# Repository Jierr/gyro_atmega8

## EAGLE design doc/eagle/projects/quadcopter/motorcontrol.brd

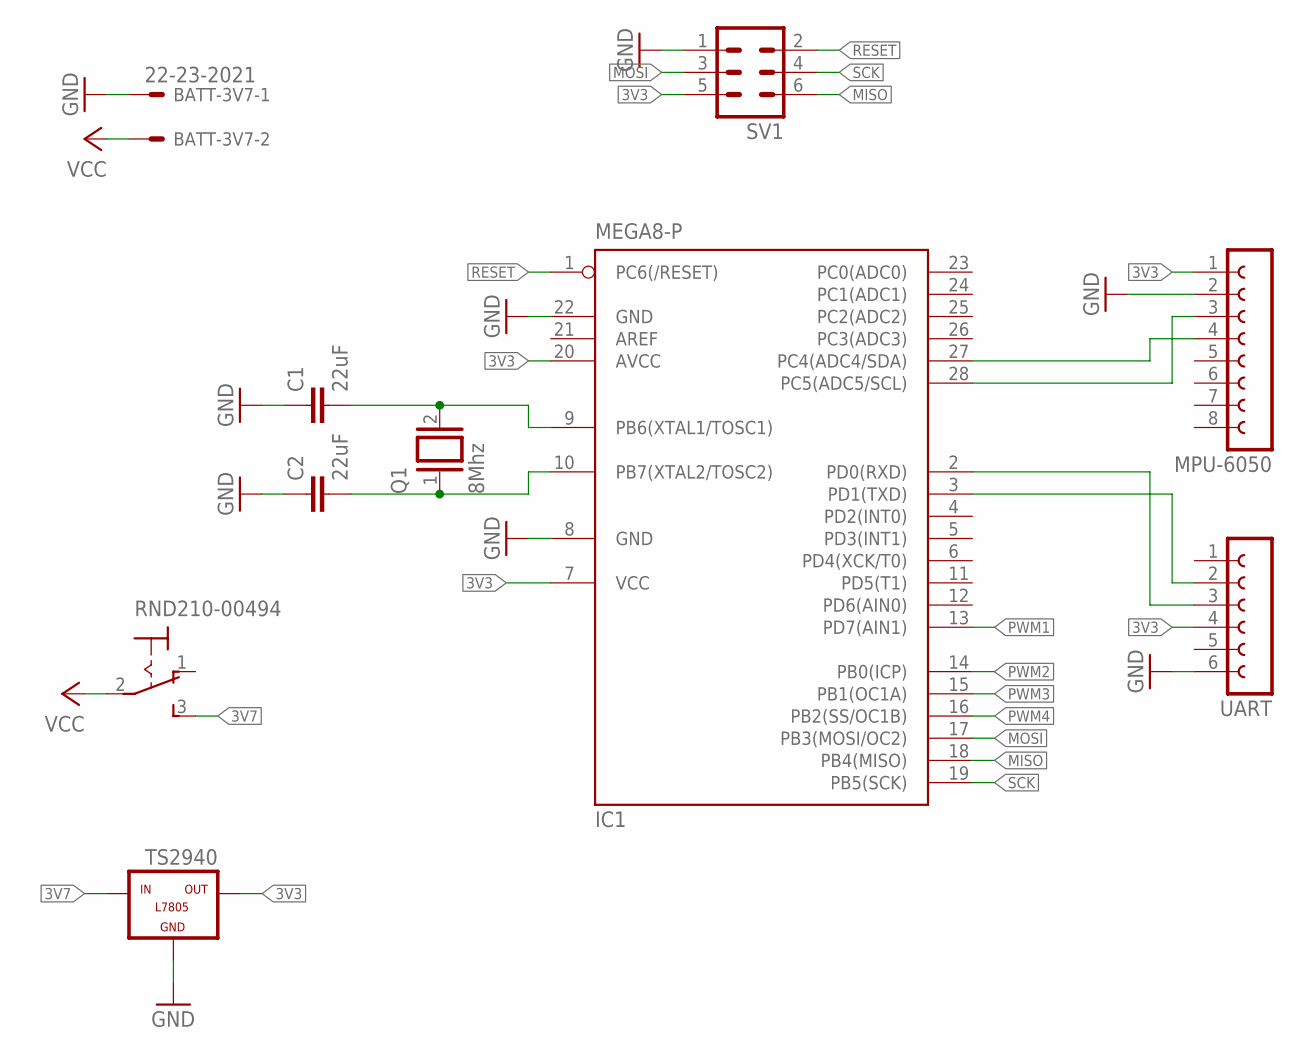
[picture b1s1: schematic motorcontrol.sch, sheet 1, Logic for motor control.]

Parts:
BATT-3V7: 22-23-2021
C1, C2: 22uF; C025-025X050
IC1: MEGA8-P; DIL28-3
MPU-6050: FE08-1; FE08
Q1: 8Mhz; QS
RND210-00494: 320-916
SV1: MA03-2
TS2940: TS2940; TO220
UART: FE06-1; FE06

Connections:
3V3: IC1.7 (VCC), IC1.20 (AVCC), MPU-6050.1, SV1.5, TS2940.3 (OUT), UART.4
3V7: RND210-00494.3 (S), TS2940.1 (IN); also elsewhere on the board
GND: BATT-3V7.1, C1.1, C2.1, IC1.8 (GND), IC1.22 (GND), MPU-6050.2, SV1.1, TS2940.2 (GND), UART.6; also elsewhere on the board
MISO: IC1.18 (PB4(MISO)), SV1.6
MOSI: IC1.17 (PB3(MOSI/OC2)), SV1.3
unnamed: C2.2, IC1.10 (PB7(XTAL2/TOSC2)), Q1.1
unnamed: C1.2, IC1.9 (PB6(XTAL1/TOSC1)), Q1.2
unnamed: IC1.28 (PC5(ADC5/SCL)), MPU-6050.3
unnamed: IC1.27 (PC4(ADC4/SDA)), MPU-6050.4
unnamed: IC1.3 (PD1(TXD)), UART.2
unnamed: IC1.2 (PD0(RXD)), UART.3
PWM1: IC1.13 (PD7(AIN1)); also elsewhere on the board
PWM2: IC1.14 (PB0(ICP)); also elsewhere on the board
PWM3: IC1.15 (PB1(OC1A)); also elsewhere on the board
PWM4: IC1.16 (PB2(SS/OC1B)); also elsewhere on the board
RESET: IC1.1 (PC6(/RESET)), SV1.2
SCK: IC1.19 (PB5(SCK)), SV1.4
VCC: BATT-3V7.2, RND210-00494.2

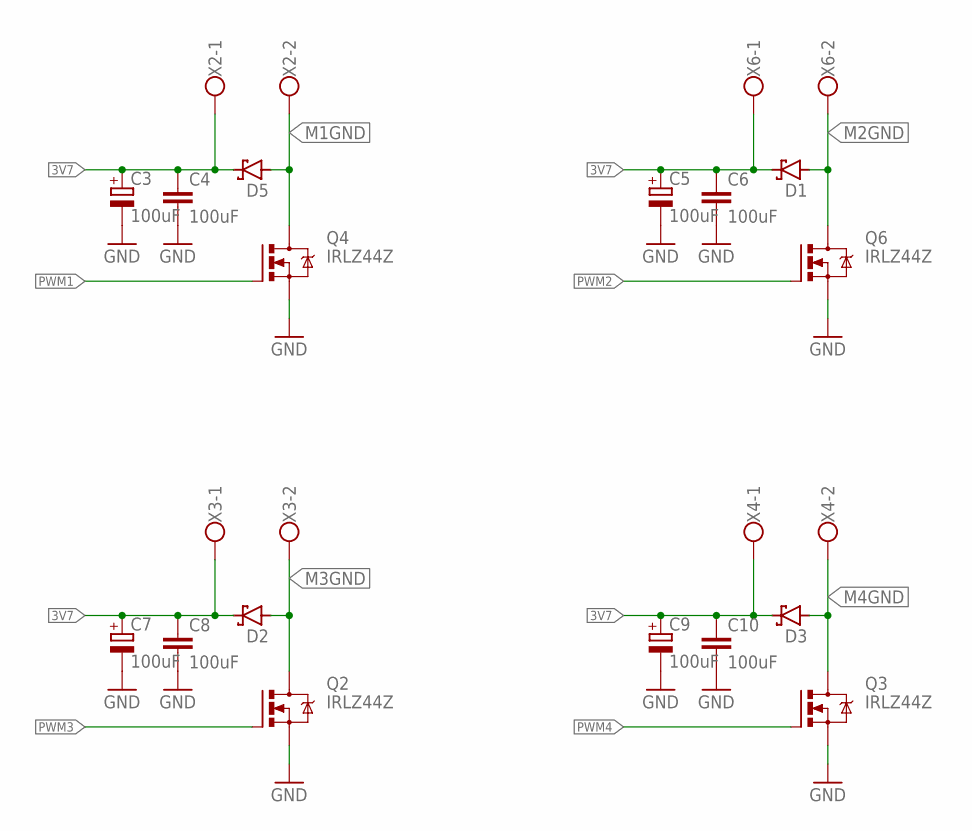
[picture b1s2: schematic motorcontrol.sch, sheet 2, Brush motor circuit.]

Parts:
C3, C5, C7, C9: 100uF; E2-5
C4, C6, C8, C10: 100uF; C025-025X050
D1, D2, D3, D5: SCHOTTKY-DIODEDO201T15; DO201T15
Q2, Q3, Q4, Q6: IRLZ44Z; TO220BH
X2, X3, X4, X6: W237-102

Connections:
3V7: C3.+, C4.1, C5.+, C6.1, C7.+, C8.1, C9.+, C10.1, D1.C, D2.C, D3.C, D5.C, X2.1, X3.1, X4.1, X6.1; also elsewhere on the board
GND: C3.-, C4.2, C5.-, C6.2, C7.-, C8.2, C9.-, C10.2, Q2.S, Q3.S, Q4.S, Q6.S; also elsewhere on the board
M1GND: D5.A, Q4.D, X2.2
M2GND: D1.A, Q6.D, X6.2
M3GND: D2.A, Q2.D, X3.2
M4GND: D3.A, Q3.D, X4.2
PWM1: Q4.G; also elsewhere on the board
PWM2: Q6.G; also elsewhere on the board
PWM3: Q2.G; also elsewhere on the board
PWM4: Q3.G; also elsewhere on the board

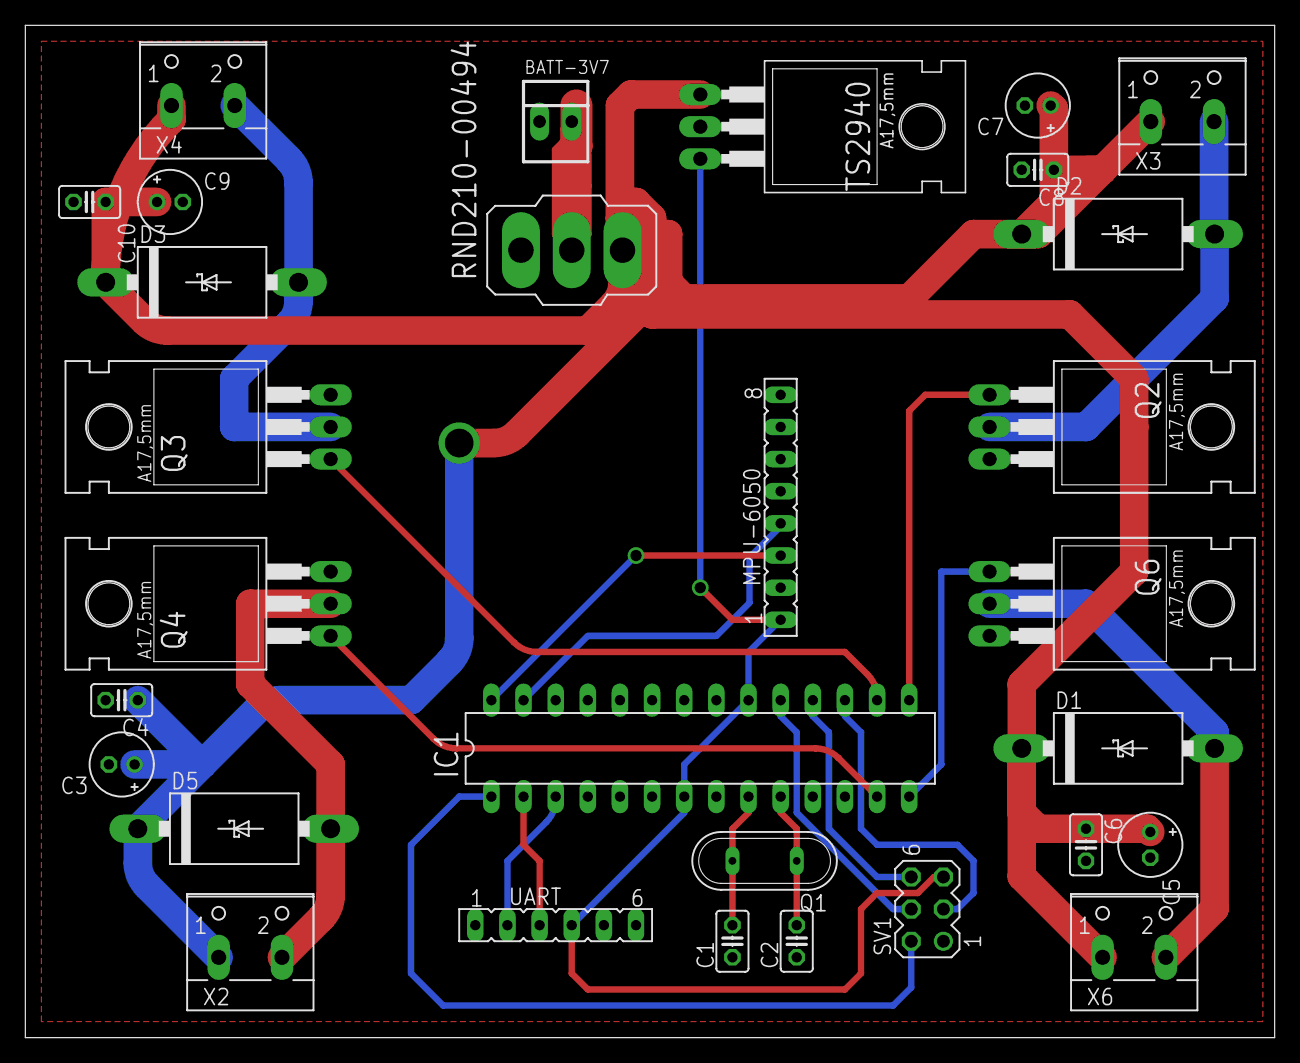
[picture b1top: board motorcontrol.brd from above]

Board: 2 copper layers, 98.7 x 80.0 mm, 30 parts (0 on the bottom side), 22 nets.

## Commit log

2016-09-13 Initial Commit. Use Atmega8 with MP6050(Gyro, Accel). Todo Kalman Filter
2016-09-13 no %
2016-09-13 base_i2c_is_ready, base_i2c_wait
2016-10-10 ignore tmpfiles
2016-10-10 8 Bit Timer0 and SW PWM
2016-10-18 More SW PWM
2016-10-18 Timer 0 works, still need callibrating for higher frequency pwm
2016-10-20 SW PWM almost done
2016-10-20 SW PWM for controlling 4 brush motors works
2016-10-20 100=100 Zyklen
2016-10-24 Wrong Index initializing Pin for SW PWM
2017-07-02 unform debug output
2017-07-15 Circuit docu
2017-07-15 renaming
2017-07-15 format
2017-07-16 Added motor control
2017-07-16 fixed Gate Source Descr.
2017-07-23 update doc
2020-08-15 Eagle and parts
2020-08-16 Update circuit
2020-08-18 PCB producable
2020-08-18 cleanup
2020-08-18 Ignore eagle backup files
2020-09-24 Fix too many Debug messages leading to stackoverflow
2020-09-24 Update project files
2020-09-24 refactor names
2020-09-27 Refactor formatting, Calculate view angle with error correction
2020-09-30 Reduce size, and retry gyro calculation -> Still is bad, noisy, need a filter
2020-10-10 Use complimentary filter to calculate Angles via Gyroscope and Accelerometer
2020-10-14 Wip flight control, state machine
2021-04-25 Add lift up initialization
2021-05-02 Test hovering sequence working
